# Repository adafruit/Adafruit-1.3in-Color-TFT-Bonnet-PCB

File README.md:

## Adafruit 1.3in Color TFT Bonnet for Raspberry Pi - 240x240 TFT + Joystick Add-on PCB

<a href="http://www.adafruit.com/products/4506"><br/>
Click here to purchase one from the Adafruit shop</a>

PCB files for the Adafruit 1.3in Color TFT Bonnet for Raspberry Pi - 240x240 TFT + Joystick Add-on.

Format is EagleCAD schematic and board layout
* https://www.adafruit.com/product/4506

### Description

If you'd like a compact color display, with buttons and a joystick - we've got what you're looking for. The Adafruit 1.3" Color TFT Bonnet for Raspberry Pi is the big sister to our mini PiTFT add-ons. This bonnet has 240x240 color pixels in an IPS TFT display controlled over SPI. This display is super small, only about 1.3" diagonal, but since it is an IPS display, it's very readable with high contrast and visibility.

With the TFT display in the center, we had some space on either side so we added a 5-way joystick and two pushbuttons. Great for when you want to have a control interface for your project. On the bottom we have a Qwiic/STEMMA QT connector for I2C sensors and device so you can plug and play any of our STEMMA QT devices.

Using the display is very easy, we have a kernel driver and Python library for the ST7789 chipset. You can set it up as a console output so you can have text and user interface through the Raspberry Pi OS or you draw images, text, whatever you like, using the Python imaging library.  We also have Python code you can use to read the joystick and buttons. Our tests showed ~15 FPS update rates so you can do animations or simple video.

Comes completely pre-assembled and tested so you don't need to do anything but plug it in and install our Python code! Works with any Raspberry Pi computer, including the original Pi 1, B+, Pi 2, Pi 3, Pi 4, and Pi Zero.

### License

Adafruit invests time and resources providing this open source design, please support Adafruit and open-source hardware by purchasing products from [Adafruit](https://www.adafruit.com)!

Designed by Limor Fried/Ladyada for Adafruit Industries.

Creative Commons Attribution/Share-Alike, all text above must be included in any redistribution.
See license.txt for additional details.

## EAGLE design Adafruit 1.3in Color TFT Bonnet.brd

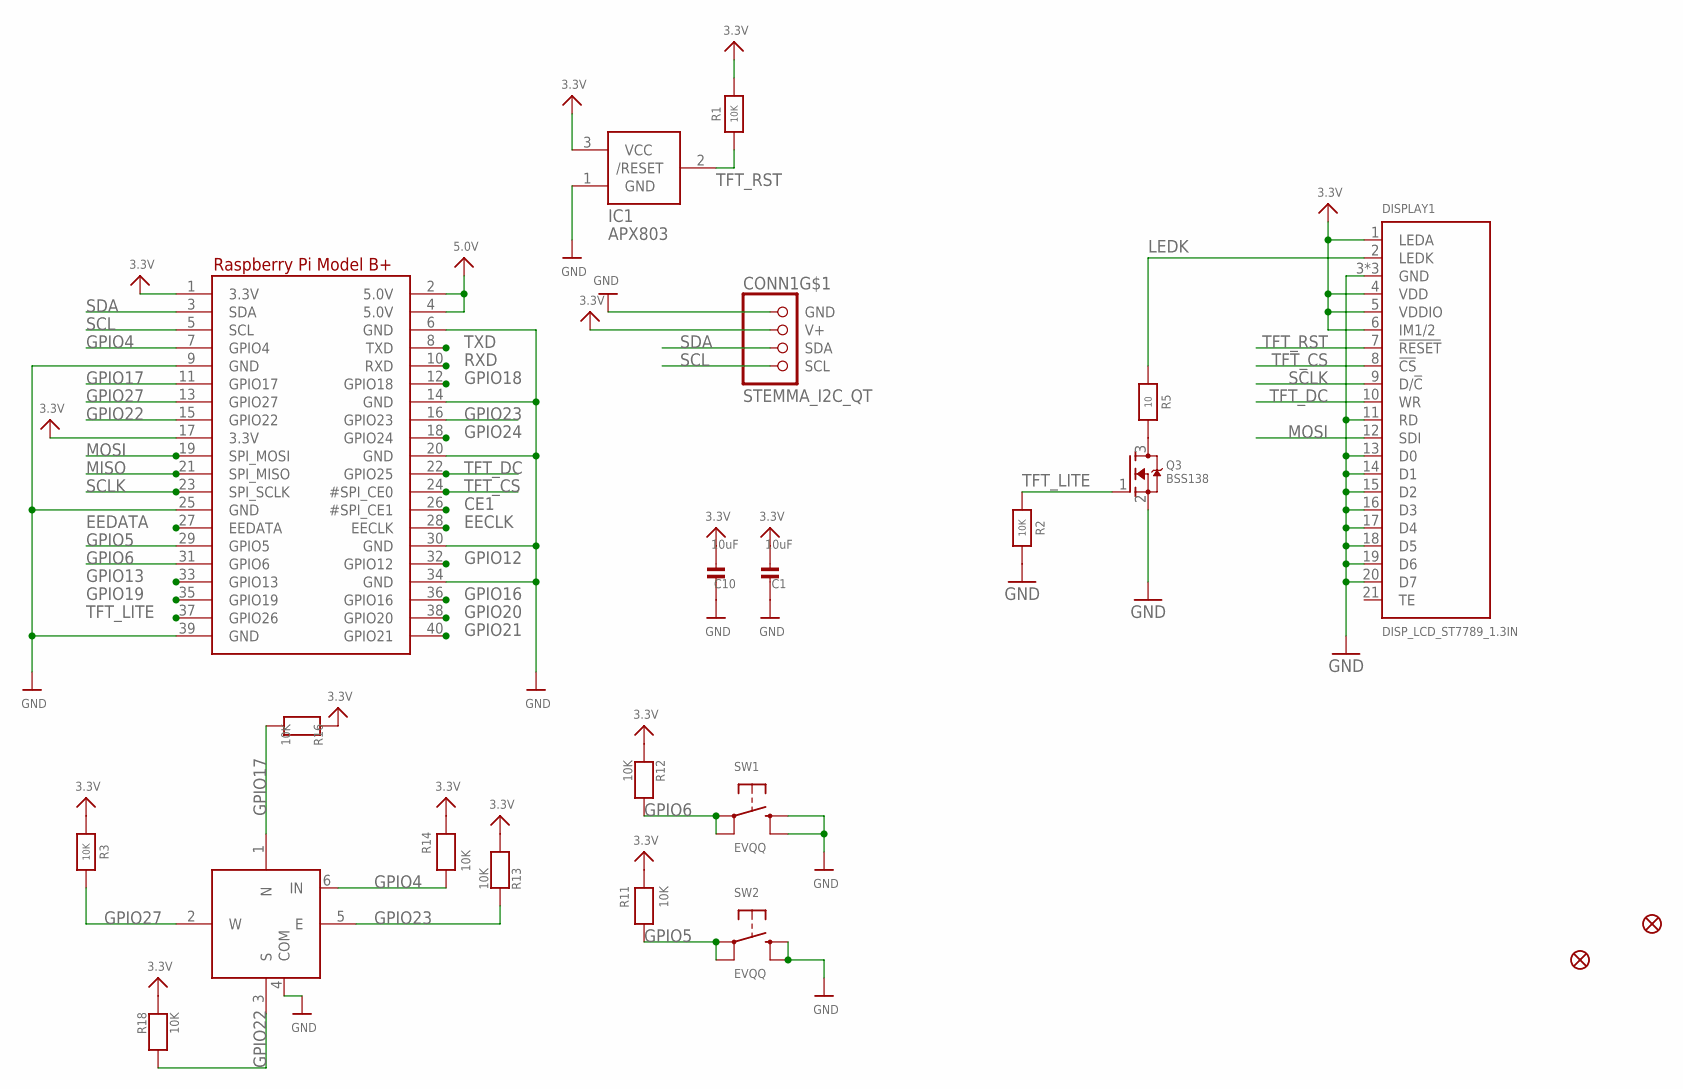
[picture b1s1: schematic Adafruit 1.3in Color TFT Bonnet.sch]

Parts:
C1, C10: 10uF; 0805-NO
CONN1: STEMMA_I2C_QT; JST_SH4
DISPLAY1: DISP_LCD_ST7789_1.3IN; TFT_1.3IN_240X240_24P
FID1, FID2: FIDUCIAL_1MM
IC1: APX803; SOT23
Q3: BSS138; SOT23-WIDE
R1, R3, R11, R12, R13, R14, R16, R18: 10K; 0805-NO
R2: 10K; 0603-NO
R5: 10; 0603-NO
RPI1: RASPBERRYPI_BPLUS_BONNETSMT; PI_BONNET_SMT
SW1: EVQQ; 6MMX6MM_TACTILE_SMT
SW2: EVQQ; 6MM_SMT
SW3: NAVSWITCHSKQUABAUE010; SKQUBAE010

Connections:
3.3V: C1.2, C10.2, CONN1.2 (V+), DISPLAY1.1 (LEDA), DISPLAY1.4 (VDD), DISPLAY1.5 (VDDIO), DISPLAY1.6 (IM1/2), IC1.3 (VCC), R1.2, R3.2, R11.2, R12.2, R13.2, R14.2, R16.1, R18.1, RPI1.1 (3.3V), RPI1.17 (3.3V)
5.0V: RPI1.2 (5.0V), RPI1.4 (5.0V)
CE1: RPI1.26 (#SPI_CE1)
EECLK: RPI1.28 (EECLK)
EEDATA: RPI1.27 (EEDATA)
GND: C1.1, C10.1, CONN1.1 (GND), DISPLAY1.3 (GND), DISPLAY1.11 (RD), DISPLAY1.13 (D0), DISPLAY1.14 (D1), DISPLAY1.15 (D2), DISPLAY1.16 (D3), DISPLAY1.17 (D4), DISPLAY1.18 (D5), DISPLAY1.19 (D6), DISPLAY1.20 (D7), DISPLAY1.23 (GND), DISPLAY1.24 (GND), IC1.1 (GND), Q3.2 (S), R2.1, RPI1.6 (GND), RPI1.9 (GND), RPI1.14 (GND), RPI1.20 (GND), RPI1.25 (GND), RPI1.30 (GND), RPI1.34 (GND), RPI1.39 (GND), SW1.B (S), SW1.B' (S1), SW2.B (S), SW2.B' (S1), SW3.4 (COM)
GPIO4: R14.1, RPI1.7 (GPIO4), SW3.6 (IN)
GPIO5: R11.1, RPI1.29 (GPIO5), SW2.A, SW2.A' (P1)
GPIO6: R12.1, RPI1.31 (GPIO6), SW1.A, SW1.A' (P1)
GPIO12: RPI1.32 (GPIO12)
GPIO13: RPI1.33 (GPIO13)
GPIO16: RPI1.36 (GPIO16)
GPIO17: R16.2, RPI1.11 (GPIO17), SW3.1 (N)
GPIO18: RPI1.12 (GPIO18)
GPIO19: RPI1.35 (GPIO19)
GPIO20: RPI1.38 (GPIO20)
GPIO21: RPI1.40 (GPIO21)
GPIO22: R18.2, RPI1.15 (GPIO22), SW3.3 (S)
GPIO23: R13.1, RPI1.16 (GPIO23), SW3.5 (E)
GPIO24: RPI1.18 (GPIO24)
GPIO27: R3.1, RPI1.13 (GPIO27), SW3.2 (W)
LEDK: DISPLAY1.2 (LEDK), R5.2
MISO: RPI1.21 (SPI_MISO)
MOSI: DISPLAY1.12 (SDI), RPI1.19 (SPI_MOSI)
unnamed: Q3.3 (D), R5.1
RXD: RPI1.10 (RXD)
SCL: CONN1.4 (SCL), RPI1.5 (SCL)
SCLK: DISPLAY1.9 (D/!C), RPI1.23 (SPI_SCLK)
SDA: CONN1.3 (SDA), RPI1.3 (SDA)
TFT_CS: DISPLAY1.8 (!CS), RPI1.24 (#SPI_CE0)
TFT_DC: DISPLAY1.10 (WR), RPI1.22 (GPIO25)
TFT_LITE: Q3.1 (G), R2.2, RPI1.37 (GPIO26)
TFT_RST: DISPLAY1.7 (!RESET), IC1.2 (/RESET), R1.1
TXD: RPI1.8 (TXD)

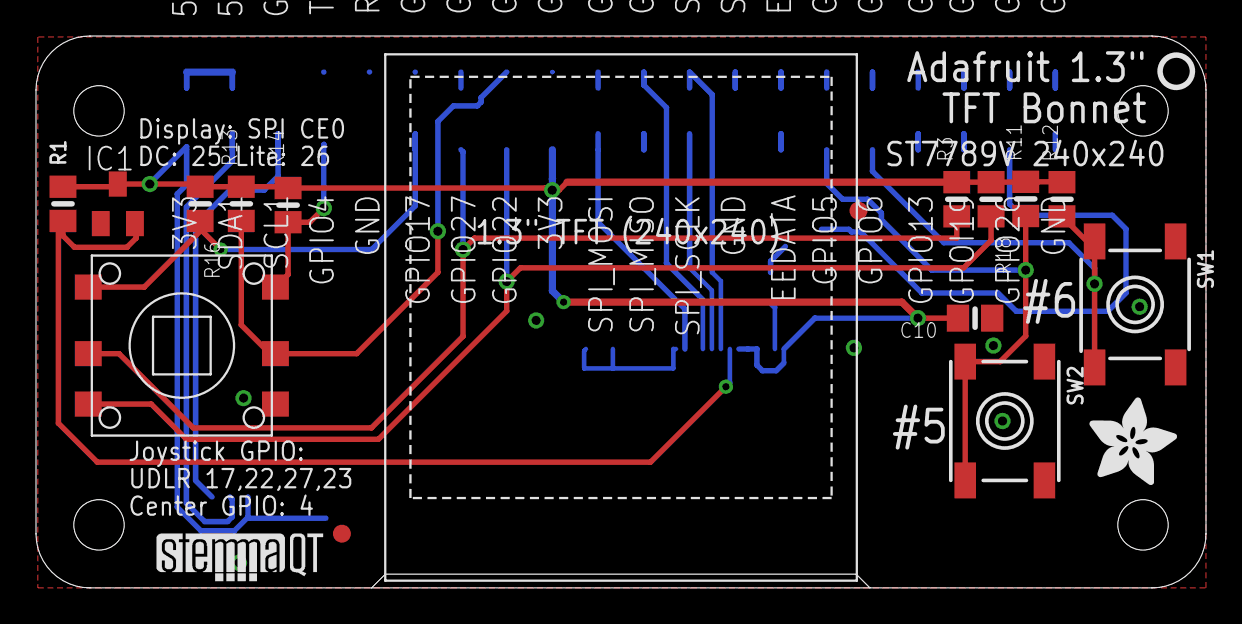
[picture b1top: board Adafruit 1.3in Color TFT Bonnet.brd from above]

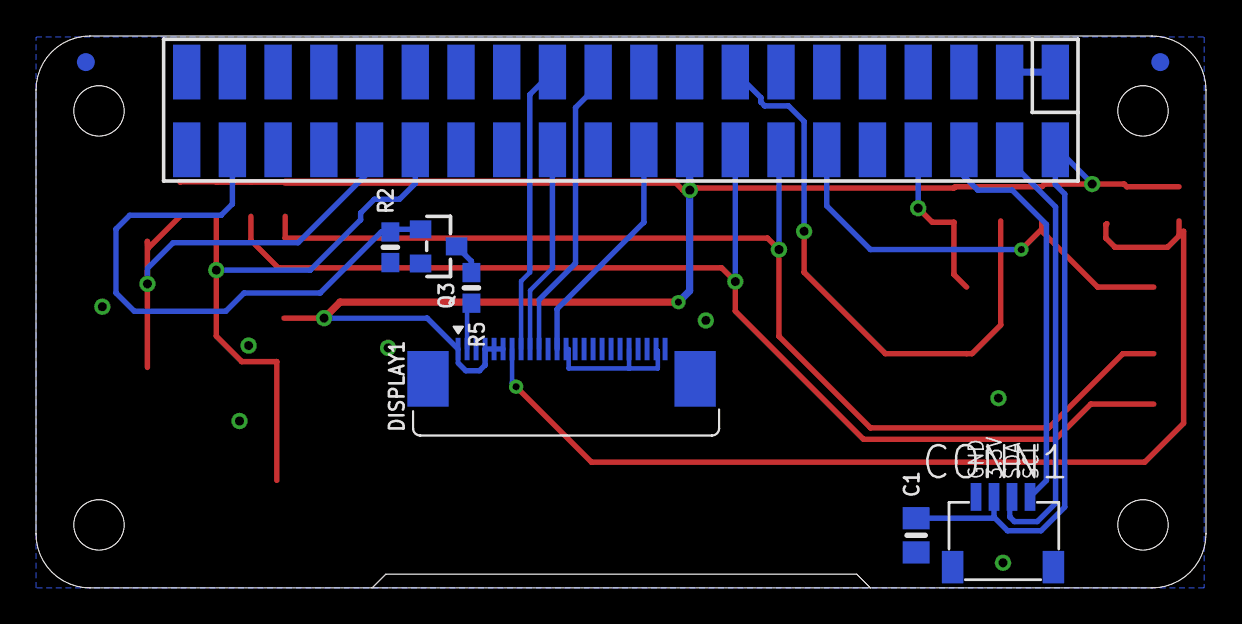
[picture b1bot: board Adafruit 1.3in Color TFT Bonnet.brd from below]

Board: 2 copper layers, 65.0 x 30.7 mm, 25 parts (6 on the bottom side), 20 nets.

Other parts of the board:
U$2: PCBFEAT-REV-040
U$28: ADAFRUIT_5MM
U$29: STEMMAQT

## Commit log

2020-06-24 Adding board files.
